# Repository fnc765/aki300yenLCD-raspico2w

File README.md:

# aki300yenLCD-raspico2w — Pico 2 W の Wi-Fi OTA リファレンス実装 (Rust / Embassy)

Raspberry Pi Pico 2 W (RP2350) で秋月電子の 300 円 LCD **LTA042B010F (400×96 RGB666 TFT)** を
PIO + DMA で駆動し、その表示を持ったファームウェアを **Wi-Fi 経由 (GitHub Release) で自己更新する**
リファレンス実装です。`no_std` の Rust と [Embassy](https://embassy.dev/) で書かれています。

## 概要

- **LCD 駆動**: PIO0 の 2 つのステートマシンが RGB666 + NCLK と HSYNC/VSYNC を出力し、DMA CH0〜CH3 の
  自走リングが 60 Hz でフレームバッファを流し続けます。CPU は垂直ブランキング中にバックバッファを
  フロントへコピーするだけで、フラッシュ消去・書き込み中 (割り込み禁止、数百 ms) でも走査は乱れません。
- **Wi-Fi OTA**: `wifi_ota` bin が SD カードの `WIFI.TXT` で Wi-Fi に接続し、60 秒ごとに GitHub Release の
  `manifest.json` を HTTPS で取得します。自分より新しい版があれば `wifi_ota.bin` を **他方の A/B 区画** に
  ストリーミング書き込みし、SHA-256 と読み戻しで検証してから RP2350 bootrom の FLASH_UPDATE 再起動で
  新版を起動します。新版は TBYB (Try Before You Buy) で起動し、Wi-Fi + DHCP が通ったら `explicit_buy` で
  確定、通らなければ bootrom のウォッチドッグで旧版に戻ります。独自ブートローダは書かず、bootrom の
  標準機能 (A/B 版数比較・FLASH_UPDATE・TBYB) だけで構成しています。
- **実機確認**: 2026-09-29 に実機 (1 台) で v0.2.6 への自動更新 (ダウンロード → 検証 →
  FLASH_UPDATE 起動 → TBYB 自己診断 → 確定) が通ることを確認しました。
- **ネットワーク・ティッカー (v0.3.0〜)**: OTA の土台の上に、NTP 時計・Open-Meteo の天気・GitHub 上の
  `message.txt` を流す表示を載せた `ticker` bin。v0.3.0 からは Release の OTA イメージがこれになり、
  `wifi_ota` 0.2.x が動いている機体もそのまま `ticker` に切り替わります ([ticker.md](docs/ticker.md))。
  v0.4.0 からは SD の写真 (BMP) をスライドショーで背景にし、その上に半透明の板で情報を重ねます。
  画面は PC のシミュレータ `tools/ui-sim` で書き込む前に確かめられます ([ui-sim.md](docs/ui-sim.md))。
  v0.5.0 からは同じ LAN のブラウザで地域 / 表示 / 流れる文字 / 写真を変えられる **設定ページ** があります
  ([settings-server.md](docs/settings-server.md))。v0.5.1 からは URL とアクセスコードが流れる文字の中に毎周流れます
  (`ticker.txt` の `show_settings=0` か設定ページで止められます)。
  v0.6.1 では、Pico 2 W が同じ LAN の Tapo P110M から Matter 経由で消費電力を読み、時計の下に表示します。
  v0.6.2 からは設定ページの「画面の向き」で画面全体を180度回転でき、デバイスを逆さに置いて使えます (SD の `rotate=180`、既定 `0`)。
  v0.6.3 のソースには電力の大型表示と推移グラフを追加し、1分〜24時間の6つの期間を設定ページから選べます。履歴は起動中に RAM に蓄積します ([ticker.md §1.4](docs/ticker.md#14-電力を大きく表示する推移を見る-063))。
  PC やクラウドの中継は不要です ([matter-power.md](docs/matter-power.md))。

## ハードウェア

| 部品 | 内容 |
|---|---|
| マイコン | Raspberry Pi Pico 2 W (RP2350A、フラッシュ 4 MB、SRAM 512 kB、CYW43439 Wi-Fi) |
| LCD | LTA042B010F 400×96 RGB666 TFT (秋月電子「300 円 LCD」)。DE 無し、HSYNC/VSYNC 同期 |
| microSD | GPIO ビットバング SPI (基板配線がハード SPI のピン組ではないため) |
| 電源 | LCD の ±13.8 V (VGON/VSS) と CCFL インバータが別途必要 ([hardware-connection.md](docs/hardware-connection.md)) |

ピン割り当て:

| 機能 | GPIO | リソース |
|---|---|---|
| LCD B5..B0 / G5..G0 / R5..R0 | GP2〜GP7 / GP8〜GP13 / GP14〜GP19 | PIO0 SM0 (OUT 18 本) |
| LCD NCLK | GP20 | PIO0 SM0 (side-set) |
| LCD HSYNC / VSYNC | GP21 / GP22 | PIO0 SM1 (SET 2 本) |
| LCD 画素 / 同期データ転送 | — | DMA CH0〜CH3 |
| microSD DAT0(MISO) / CS / CMD(MOSI) / CLK | GP0 / GP26 / GP27 / GP28 | GPIO ビットバング |
| CYW43439 PWR / DIO / CS / CLK | GP23 / GP24 / GP25 / GP29 (基板内配線) | PIO1 SM0、DMA CH4 |
| USB | — | picotool 用 reset interface (`picotool load -f`) |

LCD のタイミング (H 合計 509 clk = 表示 400 + ブランキング 109、V 合計 113 行 = 表示 96 + 17、
NCLK ≈ 3.45 MHz) は [datasheet-LTA042B010F.md](docs/datasheet-LTA042B010F.md) と `src/lcd/timing.rs` に、
配線と電源回路は [hardware-connection.md](docs/hardware-connection.md)、事前検討は
[feasibility-report.md](docs/feasibility-report.md) にあります。

## リポジトリ構成

```
src/
  lib.rs            ライブラリクレート (各 bin から共用)
  lcd/              LCD 走査層: display.rs (PIO0 + DMA リング、BackBuffer / present)、
                    timing.rs (LTA042B010F のタイミング定数)、framebuffer.rs、pio_program.rs
  wifi.rs           CYW43439 の立ち上げ (PIO1 + DMA CH4)、embassy-net (DHCP)、WIFI.TXT の読み込み
  ota/              OTA 本体: manifest.rs (manifest.json と semver 比較)、http.rs (HTTPS、302 追跡)、
                    slot.rs (書き込み先区画の決定、セクタ消去 / ページ書き込み、SHA-256、読み戻し)
  ab_boot.rs        bootrom の A/B・TBYB API (get_sys_info / get_partition_table_info / explicit_buy / reboot)
  boot_trace.rs     TBYB 起動の進行を WATCHDOG.SCRATCH5〜7 に記録し、巻き戻り後の旧版が読む
  image_def.rs      Cargo.toml の version から VERSION 項目付き IMAGE_DEF を生成 (TBYB フラグも)
  usb_reset.rs      picotool 用 USB reset interface
  sdcard.rs         microSD (GPIO SPI) と FAT ボリューム
  ota/app.rs        OTA + TBYB + 接続管理の実行部 (ticker / wifi_ota 共用)
  ticker/           ticker の部品 (暦、ticker.txt、Open-Meteo、SNTP、写真のスライドショー)
  web/              設定ページの HTTP サーバ (0.5.0〜): server.rs と、要求の解釈 / アクセスコード / BMP の検査など純粋な部品
  ui/               画面の描画 (no_std の純粋なコード、tools/ui-sim と共用): 画面構成、ガラス板、AA 数字、
                    天気アイコン、BMP の読み込み (拡大縮小 + 切り出し)
  font/shinonome.rs 東雲フォント (14 ドット日本語) の検索と描画
  bin/              下記の実行ファイル
web/settings/       設定ページ (index.html 1 枚。build.rs が gzip にしてファームに埋め込む)
partition/          A/B パーティションテーブル (pico2w-ab.json → pico2w-ab.uf2)
scripts/            make-ota-image.sh (ELF → .bin/.uf2/.sha256)、make-manifest.sh、make-partition-table.sh、
                    stack-report.py (スタック見積もり)、check-skill.py (CI: SKILL.md / CLAUDE.md の検査)
fonts/shinonome/    東雲フォント (14 ドット) のビットマップテーブルとライセンス (Public Domain)
fonts/dejavu/       時計 / 気温の AA 数字の元 (DejaVu Sans) のライセンス
ticker/message.txt  ticker が流す文字 (main を書き換えれば 5 分以内に反映)
tools/              bdf2bin.py (BDF → フォントテーブル)、ticker-tests (ホストでのユニットテスト)、
                    ui-sim (画面シミュレータ: PNG / GIF、見本の背景 BMP。docs/ui-sim.md)、
                    settings-mock (設定ページの偽の端末と画面写真。docs/settings-server.md)
.github/workflows/  build.yml (全 bin をビルド、v* タグで Release)、release.yml (workflow_dispatch で Release)
docs/               設計・手順・実機で得た知見 (下記リンク)
```

`[[bin]]` 一覧 (`Cargo.toml`):

| bin | 内容 |
|---|---|
| `ticker` | **Release の OTA イメージ (v0.3.0〜)**。NTP 時計 + Open-Meteo 天気 + `ticker/message.txt` の流れる文字 (東雲フォント 14 ドット) + OTA。v0.4.0〜 SD の BMP のスライドショーを背景に、ガラス風の板で重ね描き。設定は SD の `TICKER.TXT` ([ticker.md](docs/ticker.md))、v0.5.0〜 ブラウザの設定ページからも ([settings-server.md](docs/settings-server.md))。Release 用は `--features tbyb` |
| `wifi_ota` | OTA の最小構成 (v0.2.x の OTA イメージ)。`wifi_status` の表示 + GitHub Release からの自己更新。OTA / TBYB の本体は `src/ota/app.rs` で `ticker` と共用 |
| `wifi_status` | SD の `WIFI.TXT` で Wi-Fi に接続し、周辺 AP の RSSI を LCD に表示 ([wifi-status.md](docs/wifi-status.md)) |
| `ota_selftest` | Wi-Fi 無しで A/B・TBYB を確認する診断 bin。起動区画・版数・TBYB 状態を表示して `explicit_buy` ([ota-setup.md](docs/ota-setup.md)) |
| `ota_selftest_min` | 実機二分探索用の最小表示 bin |
| `sd_bmp_viewer` | SD の `IMAGE.BMP` / `IMAGE2.BMP` を 10 秒ずつ表示 ([sd-bmp-viewer.md](docs/sd-bmp-viewer.md)) |
| `layer0_gpio_test` 〜 `layer7_*` | LCD 駆動を段階的に作った検証用 bin (GPIO → PIO クロック → 同期 → 単色 → DMA → 全フレーム DMA)。 [layer7-fullframe-dma.md](docs/layer7-fullframe-dma.md) |
| `pico2w-300yen-lcd` | `src/main.rs` (初期の GPIO 動作確認) |

## OTA の仕組み

設計の全体は [ota-design.md](docs/ota-design.md)、`wifi_ota` の挙動と LCD の読み方は
[wifi-ota.md](docs/wifi-ota.md) にあります。要点だけ挙げます。

### A/B パーティション

`partition/pico2w-ab.json` を `picotool partition create` で UF2 にして、フラッシュ先頭に 1 回だけ書きます。

| 領域 | ストレージオフセット | サイズ | 用途 |
|---|---|---|---|
| slot 0 | 0x000000–0x000FFF | 4 kB | パーティションテーブル |
| slot 1 | 0x001000–0x001FFF | 4 kB | 予約 (テーブルの A/B 用、未使用) |
| P0 `app-a` | 0x002000–0x1E1FFF | 1920 kB | アプリ A (family `rp2350-arm-s`) |
| P1 `app-b` | 0x1E2000–0x3C1FFF | 1920 kB | アプリ B (`link: ["a", 0]` で P0 の B) |
| P2 `data` | 0x3C2000–0x3FCFFF | 236 kB | 将来の設定保存用 (起動では無視) |
| 未区画 | 0x3FD000–0x3FFFFF | 12 kB | 空き (最終ページは RP2350-E10 対策の絶対ブロック用) |

イメージは常に 0x10000000 でリンクし、どちらの区画に置かれても bootrom の QMI アドレス変換で
0x10000000 に見えるので、区画別のビルドは不要です (`memory.x` の `FLASH LENGTH = 1920K`)。

### 版数と起動選択

- `src/image_def.rs` が `Cargo.toml` の `version` から VERSION 項目付きの IMAGE_DEF を各 bin に埋め込みます
  (`0.2.6` → IMAGE_DEF `0.206`)。bootrom は A/B のうち版数の高い方を起動します。
- `--features tbyb` を付けると IMAGE_DEF に TBYB フラグが立ちます。この版は FLASH_UPDATE 起動のときだけ選ばれ、
  bootrom が 16.7 s のウォッチドッグを仕掛けた状態で起動します。`explicit_buy` を呼ぶまで確定しません。

### 更新フロー (`ticker` / `wifi_ota` 共通、`src/ota/app.rs`)

1. DHCP 完了の 5 秒後、以後 60 秒ごとに `https://github.com/<repo>/releases/latest/download/manifest.json` を取得
   (github.com の 302 → `*.githubusercontent.com` のリダイレクトは自前で追う。404 = Release 無しは正常)。
2. `{"version","bin","size","sha256"}` を読み、自分の `CARGO_PKG_VERSION` より厳密に新しいときだけ続行。
3. 書き込み先は自分が起動している区画の他方。まず先頭セクタ (IMAGE_DEF) を消して無効化。
4. manifest の `bin` (v0.3.0〜 `ticker.bin`、v0.2.x は `wifi_ota.bin`) を 4 kB ずつ受信しながらセクタ消去 →
   256 B ページ書き込み。同時に SHA-256 を計算。名前は manifest に従うので、bin の種類の切り替えも OTA でできる。
5. サイズと SHA-256 が manifest と一致し、先頭セクタの IMAGE_DEF が TBYB の RP2350 実行イメージで版数が manifest と
   一致する (1.0.1〜 `src/ota/image.rs`。manifest の `bin` も `ticker.bin` だけ) なら先頭セクタを書き、
   **0x1C000000 (アドレス変換もキャッシュも通さない XIP 窓)** から全域を読み戻してもう一度 SHA-256 を照合。
6. `reboot(FLASH_UPDATE, 対象区画)` → 新版が TBYB で起動。
7. 新版 (buy 待ち) は次が全部揃ってから 25 s 健全に動いたときだけ `explicit_buy` する (0.4.2〜 `boot_policy::BuyGate`):
   Wi-Fi join + DHCP、OTA の manifest 確認が TLS + HTTP を最後まで通った (manifest を解釈できた / 確定した HTTP ステータス)、
   `ticker` の機能を一巡 (NTP / 天気 / 文字 / SD の設定 / 最初の写真 / 0.5.0〜 設定ページの待ち受け。`wifi_ota` は一巡なし)、
   main / 取得 / 描画 (/ 設定ページの要求の処理中) の生存確認。
   起動から 180 s 以内に揃わなければウォッチドッグの再ロードをやめ、旧版に戻る。buy 待ちの OTA 確認は manifest を読むだけ。
   詳細 (ウォッチドッグ、回復モード、他方区画へ戻す) は [ticker.md §8](docs/ticker.md)。
8. 巻き戻ったとき: 新版は進行段階と稼働時間を `WATCHDOG.SCRATCH5〜7` に書き続けているので、旧版が起動時に読んで
   `WATCHDOG.REASON` や BOOT_INFO の診断ワードと共に LCD に出す。旧版は対象区画に manifest と同じイメージが
   あることから巻き戻りを検出し、10 分後に FLASH_UPDATE 起動を再試行する。
9. DNS / TLS / HTTP / フラッシュ / ハッシュの失敗は LCD に表示し、60 s → 最大 600 s のバックオフで再試行。
   検証を通らないイメージで再起動することはない。

## ビルド

```sh
rustup target add thumbv8m.main-none-eabihf     # rust-toolchain.toml が stable + rust-src + llvm-tools を指定
cargo build --release                           # 全 bin
cargo build --release --bin ticker --features tbyb     # OTA で配る (Release 用) イメージ (v0.3.0〜)
(cd tools/ticker-tests && cargo test)                   # ticker の純粋なロジックをホストでテスト
(cd tools/ui-sim && cargo test --release && cargo run --release -- --scenario scenarios/default.json --out out/)
                                                        # 画面を PC で描いて out/*.png / *.gif に (docs/ui-sim.md)
```

ELF から配布物を作るには picotool 2.x が必要です:

```sh
PICOTOOL=/path/to/picotool scripts/make-ota-image.sh target/thumbv8m.main-none-eabihf/release/ticker out
#   → out/ticker.bin (OTA 用生イメージ) / out/ticker.uf2 / out/ticker.sha256
scripts/make-manifest.sh out/ticker.bin 0.3.0 out/manifest.json
scripts/make-partition-table.sh                 # partition/pico2w-ab.uf2
```

`make-ota-image.sh` が作る UF2 には RP2350-E10 対策の「絶対ブロック」(`picotool uf2 convert --abs-block 0x103FFF00`)
が付きます。パーティションテーブルのある RP2350 A2 で BOOTSEL ドライブへドラッグ&ドロップするにはこれが
必要です ([ota-setup.md §2.1](docs/ota-setup.md))。書き込み環境 (Windows) は [setup-guide.md](docs/setup-guide.md)、
CI アーティファクトの入手は [ci-build.md](docs/ci-build.md)。

OTA で配るファーム (`ticker` など) や `src/ota`・起動の方針・ウォッチドッグ・LCD・メモリ配置・リリース手順を変えるときは、
[`.claude/skills/ota-firmware/SKILL.md`](.claude/skills/ota-firmware/SKILL.md) のチェックリスト (OTA 到達保証を壊さないための確認) に従ってください。

## 初回セットアップ

1. **パーティションテーブル (1 回だけ)**: BOOTSEL で接続し `picotool load -v partition/pico2w-ab.uf2`
   (または `pico2w-ab.uf2` を D&D)。`picotool partition info` で `app-a` / `app-b` / `data` が見えれば OK
   ([ota-setup.md §1](docs/ota-setup.md))。
2. **Wi-Fi 設定**: microSD (FAT16/32) のルートに `WIFI.TXT` を置く (1 行目 SSID、2 行目 WPA2 パスフレーズ。
   [wifi-status.md](docs/wifi-status.md))。
3. **最初のアプリ**: Release から `ticker-plain.uf2` (TBYB 無し。Wi-Fi 未設定でも起動する) を D&D するか
   `picotool load -f -v -x ticker-plain.uf2`。Wi-Fi が確実に通る機体なら `ticker.uf2` (TBYB 付き) でもよいが、
   Wi-Fi + DHCP が通らないと 16.7 s で旧版へ戻る (旧版が無ければ BOOTSEL に落ちる)。
   (`wifi_ota-plain.uf2` も同様に使える。任意で `TICKER.TXT` を SD に置く: [ticker.md §4](docs/ticker.md))
4. 以後は電源と Wi-Fi だけで更新されます。LCD の下 2 行に `ticker vX.Y.Z [via OTA] slot A/B TBYB:...` と
   `OTA: ...` の進捗が出ます ([wifi-ota.md §4](docs/wifi-ota.md)、[ticker.md §1](docs/ticker.md))。

## リリースと自動更新

1. `Cargo.toml` の `version` を上げる (IMAGE_DEF の版数は自動で追従)。
2. main にマージする。
3. Release を作る。**タグ `vX.Y.Z` の X.Y.Z と `Cargo.toml` の `version` が一致しないと CI が失敗し、Release は
   作られません。**
   - Actions → `release` → Run workflow で `version` を入力 (`gh workflow run release.yml -f version=X.Y.Z`)。
     `release.yml` が版数一致とタグ未存在を確認し、`build.yml` のビルドジョブを呼んでから注釈付きタグを打ち、
     Release にアセットを添付します。
   - または `git tag vX.Y.Z && git push origin vX.Y.Z`。`build.yml` の `push: tags` が同じことをします。
4. Release には全 bin の `.uf2` / `.bin` / `.sha256`、`pico2w-ab.uf2`、そして `--features tbyb` でビルドした
   `ticker.bin` / `ticker.uf2` (と `wifi_ota.bin` / `wifi_ota.uf2`) と、`ticker.bin` を指す `manifest.json` が付きます。
   実機は常に `releases/latest/download/<name>` を見るので、アセット名に版数は入れません。
5. 稼働中の機体は 60 秒以内に manifest を見に行き、新しければ更新 → 再起動 → 自己診断 → 確定します。

## 実機で学んだこと

- **RP2350-E10**: パーティションテーブルがある A2 機体では、UF2 の先頭に絶対ブロックが無いと BOOTSEL ドライブへの
  D&D が「何も起きない」形で失敗する。`picotool load` (PICOBOOT) は影響を受けない。
- **DMA が読むメモリはフラッシュ操作中は SRAM だけ**: フラッシュ消去・書き込み中は XIP 窓への DMA アクセスが
  バスフォールトになり、そのチャネルは停止したままになる。HSYNC/VSYNC 用のテーブルが `.rodata` にあったときは
  `explicit_buy` 1 回で画面が砂嵐になった。`#[link_section = ".data…"]` で RAM に置いて解決。
- **embassy の `Pio` ハンドルは drop しない**: `Common` / `StateMachine` の最後の drop で PIO が使っていた GPIO の
  FUNCSEL が NULL に戻り、LCD も CYW43 も止まる。`mem::forget` で保持する。
- **GitHub の 302 応答ヘッダは 5〜6 kB**: Content-Security-Policy と Set-Cookie で膨らむので、HTTP 受信バッファは
  8 kB にした。アセット配信ホストは RSA 4096 の証明書で、embedded-tls の `rsa` feature (alloc) 無しでは TLS 1.3 の
  ハンドシェイクが成立しない。
- **TBYB のウォッチドッグは 16.7 s (24 bit × 1 µs)**: Wi-Fi join + DHCP はこれに収まらないことがあるので、buy 待ちの
  間は 2 s ごとに `WATCHDOG.LOAD` を再ロードして延長した。自己診断の締め切りは 0.4.1 までは 120 s (0.4.2 から 180 s、buy 条件も強化。上の更新フロー 7)。
- **温かい再起動で CYW43439 が状態を引き継ぐ**: FLASH_UPDATE 再起動後、join は通るのに DHCP が一度も通らなかった。
  起動時に WL_REG_ON を 500 ms 落としてコールドスタートさせ、再起動前にも `leave()` + 電源断をする。
- **DHCP タイムアウトでは再 join する**: 20 s で IP が取れなければ AP から離脱してやり直す。
- **表示開始位置は名目値より 2 ワード右**: HSYNC/VSYNC 用の SM1 は有効化直後に 2 命令進んだ状態で止まるので、
  多チャネル同時トリガ後は SM0 (画素) より 2 NCLK 先行し、LCD の最初の表示画素はフレーム行の x=106 になる
  (名目 108、旧値 98 では左端 1 文字が欠けた)。v0.2.7 の目盛り表示で実機確認し、v0.2.8 から正式値。
- **OTA の経路が壊れた版は自分では直せない**: 0.4.0 は buy (Wi-Fi + DHCP だけで判定) の後、最初の HTTPS でスタックが
  溢れて固まり、OTA も同じ TLS の経路なので USB で書き直すしかなかった。0.4.2 から buy 条件に「OTA の manifest 確認が
  TLS + HTTP を最後まで通った」と機能の一巡 + 25 s を入れ、ウォッチドッグを main の最初から動かし、buy の後で落ち続ける版は
  回復モード (Wi-Fi + OTA だけ) → 他方区画へ、と段階的に戻す ([ticker.md §8](docs/ticker.md))。

## 既知の制限・今後

- **TLS はサーバ証明書を検証していない** (`TlsVerify::None`)。reqwless 0.14 / embedded-tls 0.18 の検証器がワイルドカード
  証明書を扱えないため。経路上の攻撃者が任意のファームウェアを配れるので、**信頼できる LAN でだけ使うこと**。
  第 3 段階として manifest への Ed25519 署名 (公開鍵をファームウェアに埋め込み) を予定
  ([wifi-ota.md §6](docs/wifi-ota.md))。
- OTA で配れるのは manifest が指す 1 つの bin (v0.3.0〜 `ticker`)。他の bin は USB (picotool / D&D) で書く。
- 実機確認は 1 台のみ。複数台・長期運用・フラッシュ書き込み中の cyw43 の挙動などは未確認
  ([wifi-ota.md §8](docs/wifi-ota.md))。
- 設定ページ (0.5.0〜) は LAN の中の平文の HTTP。アクセスコードと Host / Origin の確認でよそのサイトからの操作は防ぐが、
  同じ LAN で通信を見られる人からは守れない ([settings-server.md §4](docs/settings-server.md))。
  0.5.1〜 の既定 (`show_settings=1`) ではコードが LCD に常に流れるので、LCD を見られる人は誰でも設定を変えられる。
- パーティションテーブル自体の更新、Wi-Fi ファームウェア (cyw43、約 231 kB) の分離配布は扱っていない。

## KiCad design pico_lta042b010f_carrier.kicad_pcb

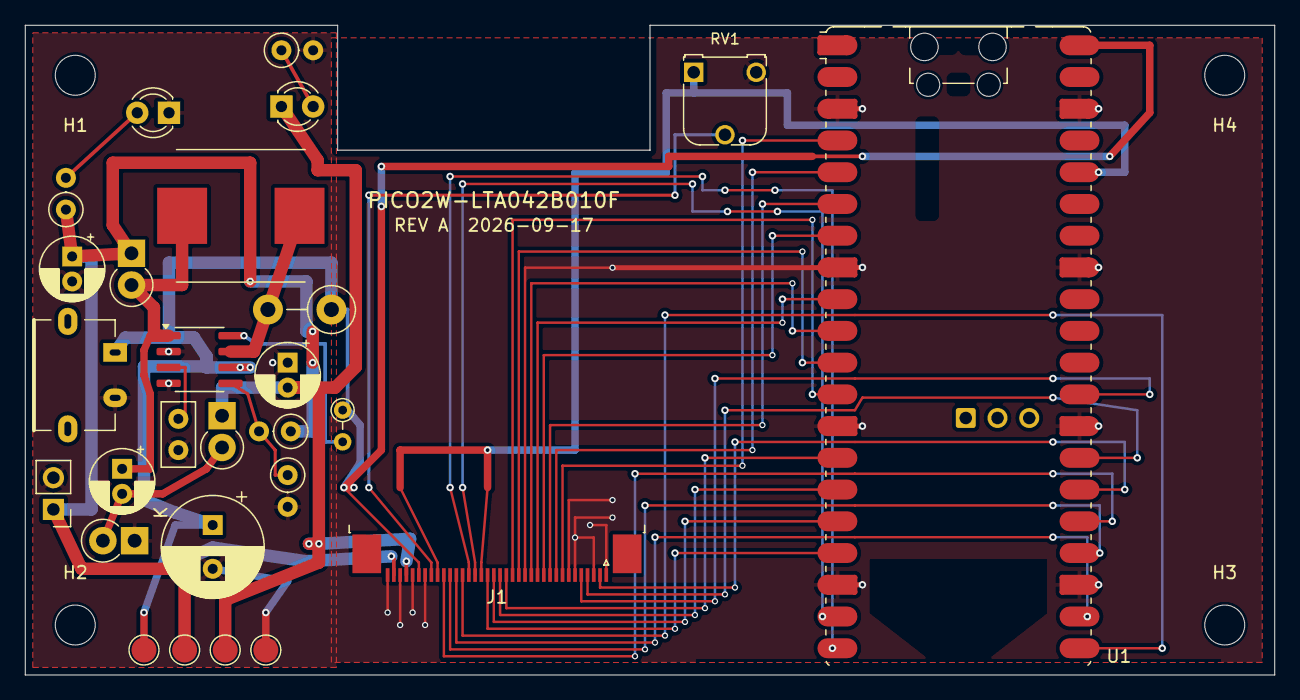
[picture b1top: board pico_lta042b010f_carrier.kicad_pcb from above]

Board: 2 copper layers, 100.0 x 52.0 mm, 31 parts (0 on the bottom side), 35 nets.

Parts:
C6: 220uF 35V; CP_Radial_D8.0mm_P3.50mm
C7: 470pF 50V C0G; C_Disc_D5.0mm_W2.5mm_P2.50mm
C8: 47uF 35V; CP_Radial_D5.0mm_P2.00mm
C9: 10uF 50V; CP_Radial_D5.0mm_P2.00mm
C11: 10uF 50V (+ to GND); CP_Radial_D5.0mm_P2.00mm
D4, D6, D7: 1N5819; D_DO-41_SOD81_P2.54mm_Vertical_KathodeUp
D5: GREEN LED 3mm; LED_D3.0mm
D8: RED LED 3mm; LED_D3.0mm
H1, H2, H3, H4: MountingHole; MountingHole_3.2mm_M3
J1: LTA042B010F_FFC_36P_0.5mm; TE_3-1734839-6_1x36-1MP_P0.5mm_Horizontal
J2: USB-C 5V INPUT; A295_CTRPB_1
J3: CCFL_INVERTER_13V8; PinHeader_1x02_P2.54mm_Vertical
L1: 100uH; L_Taiyo-Yuden_NR-10050_9.8x10.0mm_HandSoldering
R7: 0.47R 1%; R_Axial_DIN0411_L9.9mm_D3.6mm_P5.08mm_Vertical
R8: 200 1%; R_Axial_DIN0204_L3.6mm_D1.6mm_P2.54mm_Vertical
R9, R11, R16: 10k 0.1%; R_Axial_DIN0207_L6.3mm_D2.5mm_P2.54mm_Vertical
R10: 1k 0.1%; R_Axial_DIN0207_L6.3mm_D2.5mm_P2.54mm_Vertical
RV1: 10k_CONTRAST_TRIM; Potentiometer_Runtron_RM-065_Vertical
TP1: +5V; TestPoint_Pad_D2.0mm
TP2: +13V8; TestPoint_Pad_D2.0mm
TP3: -13V8; TestPoint_Pad_D2.0mm
TP4: GND; TestPoint_Pad_D2.0mm
U1: RaspberryPi_Pico_2W; RaspberryPi_Pico_W_SMD_HandSolder
U3: MC34063AD; SOIC-8_3.9x4.9mm_P1.27mm

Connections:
+3V3: J1.21 (DVDD), J1.28 (AVDD), RV1.1 (HIGH), U1.36 (3V3_OUT)
+5V: C6.1 (+), J1.31 (GVDD), J2.1 (VBUS), R7.1, R8.1, TP1.1 (+5V), U1.40 (VBUS), U3.6 (VCC)
+13V8: C8.1 (+), D4.1 (K), J1.35 (VGON), J3.1 (+13V8), R9.1, R11.1, TP2.1 (+13V8)
-13V8: C11.2 (-), D7.1 (K), D8.1, J1.33 (VSS), TP3.1 (-13V8)
CPUMP_MID: C9.2 (-), D6.2 (A), D7.2 (A)
DRIVER_DC: R8.2, U3.8 (DC)
GND: C6.2 (-), C7.2, C8.2 (-), C11.1 (+), D5.1, D6.1 (K), J1.1 (TEST_FIXED_LOW), J1.3 (GND), J1.6 (UNKNOWN_FIXED_LOW), J1.7 (GND), J1.14 (GND), J1.30 (GND), J1.32 (GND), J1.34 (GND), J1.36 (GND), J2.2 (GND), J3.2 (GND), R10.2, R16.2, RV1.3 (LOW), TP4.1 (GND), U1.3 (GND), U1.8 (GND), U1.13 (GND), U1.18 (GND), U1.23 (GND), U1.28 (GND), U1.33 (GND), U1.38 (GND), U3.2 (SWE), U3.4 (GND)
IPK_SENSE: L1.1, R7.2, U3.7 (Ipk)
LCD_B0: J1.13 (B0), U1.10 (GP7)
LCD_B1: J1.12 (B1), U1.9 (GP6)
LCD_B2: J1.11 (B2), U1.7 (GP5)
LCD_B3: J1.10 (B3), U1.6 (GP4)
LCD_B4: J1.9 (B4), U1.5 (GP3)
LCD_B5: J1.8 (B5), U1.4 (GP2)
LCD_G0: J1.20 (G0), U1.17 (GP13)
LCD_G1: J1.19 (G1), U1.16 (GP12)
LCD_G2: J1.18 (G2), U1.15 (GP11)
LCD_G3: J1.17 (G3), U1.14 (GP10)
LCD_G4: J1.16 (G4), U1.12 (GP9)
LCD_G5: J1.15 (G5), U1.11 (GP8)
LCD_HSYNC: J1.4 (HSYNC), U1.27 (GP21)
LCD_NCLK: J1.2 (NCLK), U1.26 (GP20)
LCD_R0: J1.27 (R0), U1.25 (GP19)
LCD_R1: J1.26 (R1), U1.24 (GP18)
LCD_R2: J1.25 (R2), U1.22 (GP17)
LCD_R3: J1.24 (R3), U1.21 (GP16)
LCD_R4: J1.23 (R4), U1.20 (GP15)
LCD_R5: J1.22 (R5), U1.19 (GP14)
LCD_VSYNC: J1.5 (VSYNC), U1.29 (GP22)
NEG_LED_N: D8.2, R16.1
PWR_LED_P: D5.2, R11.2
SW_NODE: C9.1 (+), D4.2 (A), L1.2, U3.1 (SWC)
TC_TIMING: C7.1, U3.3 (TC)
VCPP_ADJ: J1.29 (VCPP_ADJ), RV1.2 (WIPER)
VFB: R9.2, R10.1, U3.5 (VFB)

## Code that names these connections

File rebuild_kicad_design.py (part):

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            ]
        )

    for pin_y, name in [(96.52, "LCD_VSYNC"), (99.06, "LCD_HSYNC")]:
        add_control_stub(110.49, pin_y, 102.87, name, "left")
    add_control_stub(125.73, 101.60, 133.35, "LCD_NCLK", "right")
    for pin_y, name in [(142.24, "LCD_VSYNC"), (144.78, "LCD_HSYNC"), (149.86, "LCD_NCLK")]:
        add_control_stub(248.92, pin_y, 238.76, name, "left")
    root.extend(block for block in lcd_signal_blocks if block)

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        # Power labels are kept only at the rails and off-board interfaces;
        # the component-to-component nets are visibly wired.
        hidden_label("+5V", 127.00, 82.55),
        hidden_label("IPK_SENSE", 179.07, 96.52),
        hidden_label("TC_TIMING", 149.86, 106.68), hidden_label("+13V8", 190.50, 82.55),
        hidden_label("VFB", 195.58, 116.84), hidden_label("PWR_LED_P", 224.79, 102.87),
        hidden_label("CPUMP_MID", 242.57, 104.14), hidden_label("NEG_LED_N", 299.72, 123.19),
        hidden_label("+5V", 158.75, 96.52), hidden_label("IPK_SENSE", 153.67, 82.55),
        hidden_label("IPK_SENSE", 160.02, 82.55), hidden_label("SW_NODE", 167.64, 82.55),
        hidden_label("+13V8", 184.15, 82.55), hidden_label("GND", 168.91, 114.30),
        hidden_label("GND", 179.07, 106.68), hidden_label("GND", 149.86, 119.38),
        hidden_label("GND", 190.50, 97.79), hidden_label("+13V8", 208.28, 90.17),
        hidden_label("GND", 208.28, 119.38), hidden_label("+13V8", 224.79, 90.17),
        hidden_label("GND", 224.79, 110.49), hidden_label("SW_NODE", 242.57, 92.71),
        hidden_label("CPUMP_MID", 247.65, 110.49), hidden_label("GND", 247.65, 118.11),
        hidden_label("-13V8", 264.16, 104.14), hidden_label("-13V8", 278.13, 110.49),
        hidden_label("GND", 278.13, 118.11), hidden_label("GND", 274.32, 156.21),
        hidden_label("GND", 279.40, 184.15), hidden_label("DRIVER_DC", 153.67, 99.06),
        hidden_label("GND", 134.62, 102.87),
        hidden_label("GND", 130.81, 109.22), hidden_label("+5V", 146.05, 99.06),
        hidden_label("+5V", 130.81, 101.60),
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        label("+3V3", 279.40, 168.91), label("GND", 125.73, gnd_y),
        label("GND", 279.40, 190.50),
        label("+13V8", 196.85, plus_y, 180),
        label("-13V8", 285.75, 104.14, 180), hidden_label("SW_NODE", 176.53, 82.55, 180),
        hidden_label("SW_NODE", 179.07, 101.60), label("+13V8", 270.51, 153.67),
        label("VCPP_ADJ", 287.02, 180.34),
    ])
    root.extend([
        power_symbol("power:+5V", "#PWR0101", 127.00, 82.55),
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        if net == "DRIVER_DC":
            # U3 pin 8 to the R8 driver resistor is a short local connection.
            # Bring both ends to B.Cu outside the SOIC pin field; routing a
            # direct F.Cu diagonal through the pin row would cross SW_NODE.
            u3 = next(item for item in endpoints if item[:2] == ("U3", "8"))
            r8 = next(item for item in endpoints if item[:2] == ("R8", "2"))
            u3_via = (90.0, 33.095)
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
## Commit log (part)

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2026-02-09 init commit
2026-02-10 feat: Layer 2まで実装
2026-02-10 feat: layer3まで実装
2026-02-11 feat: Layer 4 DMA カラーバー実装 + Layer 3 オフセット修正
    - src/bin/layer4_dma_colorbar.rs: DMA スキャンライン転送カラーバーテスト新規作成
    - SM0: DMA dma_push() でピクセル自動転送 (CPU負荷ゼロ)
    - SM1: CPU wait_push() で225 words/frameタイミング供給
    - SMPTE 8色カラーバーパターン表示
    - NCLK停止リスク実質解消 (FIFO 2.3μs > CPU 0.3-0.7μs)
    - src/bin/layer3_solid_color.rs: プレフィルオフセット補正
2026-02-11 fix: Layer 1 ピン方向(Output)設定の欠落を修正
    - set_pin_dirs(Direction::Out) が未設定のため GP20 に信号が出力されなかった
    - Direction の import 追加
    - Layer 2-4 では正しく設定済みだった
2026-02-11 fix: Layer 2 FIFO overflow + 位相ずれバグ修正
    - FifoJoin::TxOnly 追加 (TX FIFO 4→8エントリ)
    - CPU ループの位相をプレフィルと整合するよう修正
    - frame_count wrapping_add に変更
2026-02-11 fix: Layer 3/4 SM1 CPU ループ位相ずれバグ修正
    - SM1 ループを 0..V_NORMAL_LINES(111) → 1..V_NORMAL_LINES(110) に修正
    - 通常ライン#1 は SM0 ピクセルのみ供給 (SM1 はプレフィル/前ループ末尾で供給済み)
    - フレーム末尾に次フレーム通常ライン#1の SM1 データ (2値) を追加
    - SM1 値数: 220 + 3 + 2 = 225/frame (PIO pull数と一致)
2026-02-11 Layer 5: framebuffer + double buffering
    - Add src/lcd/framebuffer.rs: FrameBuffer struct with 512x96 padded layout
    - rgb666/reverse6 helpers (moved from layer3/4 inline)
    - set_pixel/get_pixel with bounds check + debug_assert
    - row_slice for DMA transfer with debug_assert
    - clear for active region only
    - Add src/bin/layer5_framebuffer.rs: double-buffered display
2026-02-11 docs: update implementation plan and setup guide for Layer 5
    - Mark Layer 5 as completed in implementation-plan.md
    - Add framebuffer architecture details (512x96 padded, Channel-based double buffering)
    - Add memory usage stats (384KB/520KB = 74%)
    - Add layer5_framebuffer build target to setup-guide.md
2026-02-11 Layer 6: embedded-graphics DrawTarget implementation
    - Add DrawTarget<Color=Rgb666> impl to FrameBuffer
    - draw_iter: coordinate clipping with bounds constants
    - fill_solid: optimized slice fill with Rectangle intersection
    - clear: active region only, padding preserved
    - Add OriginDimensions impl (400x96)
    - Add src/bin/layer6_drawtest.rs: text, shapes, colorbar demo
2026-02-11 docs: update for Layer 6 completion, all layers 0-6 done
    - Mark Layer 6 as completed in implementation-plan.md
    - Add DrawTarget/OriginDimensions implementation details
    - Note all layers (0-6) completed
    - Add layer6_drawtest build target to setup-guide.md
2026-02-11 fix: NCLK sideset反転でテキスト描画崩れを修正
    LCD (LTA042B010F) はNCLKの立ち下がりエッジでデータをサンプルする。
    旧PIOプログラムでは `out pins, 18 side 0` でデータ変更とNCLK立ち下がりが
    同時に発生し、セットアップ時間が0だった。
    sideset値を反転 (side 0/1 → side 1/0) することで、データ出力時はNCLK=HIGH
    （セットアップ期間）、その後のnopでNCLK=LOW（立ち下がりエッジ）とすることで
    約145nsのセットアップ時間を確保。
2026-02-12 feat: Layer 7 全フレームDMA転送方式を追加
    - SM0（ピクセル+NCLK）とSM1（HSYNC/VSYNC）をMULTI_CHAN_TRIGGERで同時DMA起動
    - フレームバッファを512×112に拡張（V-blank 16行含む）
    - SM1タイミングデータ（225ワード）の一括DMA転送
    - 行間のCPU介入を排除しジッターを大幅軽減
    - DMA再設定をクリティカルセクションで保護
    残存する1ピクセルブレは配線品質が主因（クロック1/3で検証済み）
2026-02-16 docs(lcd): PIOプログラムのサイドセット極性ドキュメントを修正
    - pio_program.rs のコメント中の極性記述をLayer7実装と整合
    - side 1 (NCLK=HIGH) でデータセットアップ
    - side 0 (NCLK=LOW) への立ち下がりでLCDサンプル
    - コード変更なし(ドキュメントのみ)
2026-02-17 feat(layer7): add LCD performance HUD metrics and docs updates
